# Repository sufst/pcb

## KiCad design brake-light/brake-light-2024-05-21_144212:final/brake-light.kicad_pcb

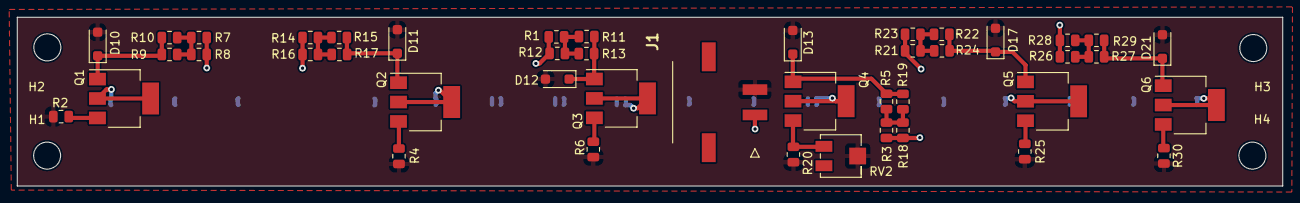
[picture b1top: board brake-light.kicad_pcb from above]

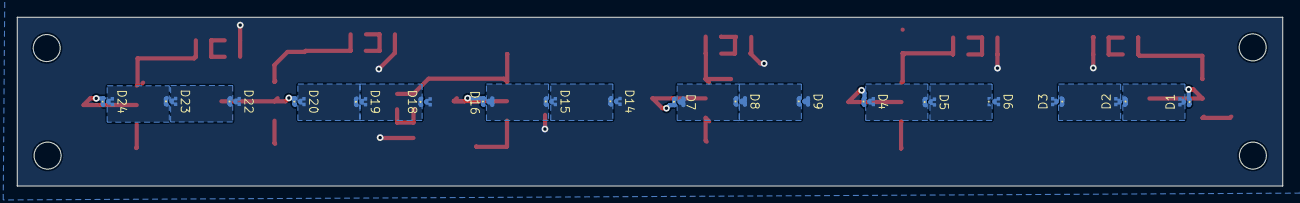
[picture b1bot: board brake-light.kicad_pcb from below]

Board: 2 copper layers, 150.0 x 20.0 mm, 66 parts (18 on the bottom side), 38 nets.

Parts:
D1, D2, D3, D4, D5, D6, D7, D8, D9, D14, D15, D16, D18, D19, D20, D22, D23, D24: KR-SITQA1.23; KR-SITQA1.23_reflow
D10, D11, D12, D13, D17, D21: 1N5333B; D_SOD-123F
H1, H2, H3, H4: MountingHole; MountingHole_3.2mm_M3
J1: LED; Molex_Micro-Fit_3.0_43650-0214_1x02_P3.00mm_Horizontal
Q1, Q2, Q3, Q4, Q5, Q6: BCP56; SOT-223-3_TabPin2
R1, R3, R5, R7, R8, R9, R10, R11, R12, R13, R14, R15, R16, R17, R18, R19, R21, R22, R23, R24, R26, R27, R28, R29: 2.7k; R_0805_2012Metric
R2, R4, R6, R20, R25, R30: 68; R_0805_2012Metric
RV2: R_Potentiometer_Trim; Potentiometer_Bourns_3224J_Horizontal

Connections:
/LED+: D3.2 (A), D6.2 (A), D9.2 (A), D14.2 (A), D18.2 (A), D22.2 (A), J1.1, R1.1, R3.1, R7.1, R8.1, R12.1, R14.1, R16.1, R18.1, R21.1, R23.1, R26.1, R28.1
/LED-: D10.2 (A), D11.2 (A), D12.2 (A), D13.2 (A), D17.2 (A), D21.2 (A), J1.2, R2.2, R4.2, R6.2, R20.2, R25.2, R30.2, RV2.2
unnamed: D1.2 (A), D2.1 (K)
unnamed: D1.1 (K), Q1.2 (C)
unnamed: D2.2 (A), D3.1 (K)
unnamed: D4.2 (A), D5.1 (K)
unnamed: D4.1 (K), Q2.2 (C)
unnamed: D5.2 (A), D6.1 (K)
unnamed: D7.2 (A), D8.1 (K)
unnamed: D7.1 (K), Q3.2 (C)
unnamed: D8.2 (A), D9.1 (K)
unnamed: D10.1 (K), Q1.1 (B), R9.2, R10.2
unnamed: D11.1 (K), Q2.1 (B), R15.2, R17.2
unnamed: D12.1 (K), Q3.1 (B), R11.2, R13.2
unnamed: D13.1 (K), Q4.1 (B), R5.2, R19.2
unnamed: D14.1 (K), D15.2 (A)
unnamed: D15.1 (K), D16.2 (A)
unnamed: D16.1 (K), Q4.2 (C)
unnamed: D17.1 (K), Q5.1 (B), R22.2, R24.2
unnamed: D18.1 (K), D19.2 (A)
unnamed: D19.1 (K), D20.2 (A)
unnamed: D20.1 (K), Q5.2 (C)
unnamed: D21.1 (K), Q6.1 (B), R27.2, R29.2
unnamed: D22.1 (K), D23.2 (A)
unnamed: D23.1 (K), D24.2 (A)
unnamed: D24.1 (K), Q6.2 (C)
unnamed: Q1.3 (E), R2.1
unnamed: Q2.3 (E), R4.1
unnamed: Q3.3 (E), R6.1
unnamed: Q4.3 (E), R20.1, RV2.3
unnamed: Q5.3 (E), R25.1
unnamed: Q6.3 (E), R30.1
unnamed: R1.2, R11.1, R12.2, R13.1
unnamed: R7.2, R8.2, R9.1, R10.1
unnamed: R14.2, R15.1, R16.2, R17.1
unnamed: R3.2, R5.1, R18.2, R19.1
unnamed: R21.2, R22.1, R23.2, R24.1
unnamed: R26.2, R27.1, R28.2, R29.1

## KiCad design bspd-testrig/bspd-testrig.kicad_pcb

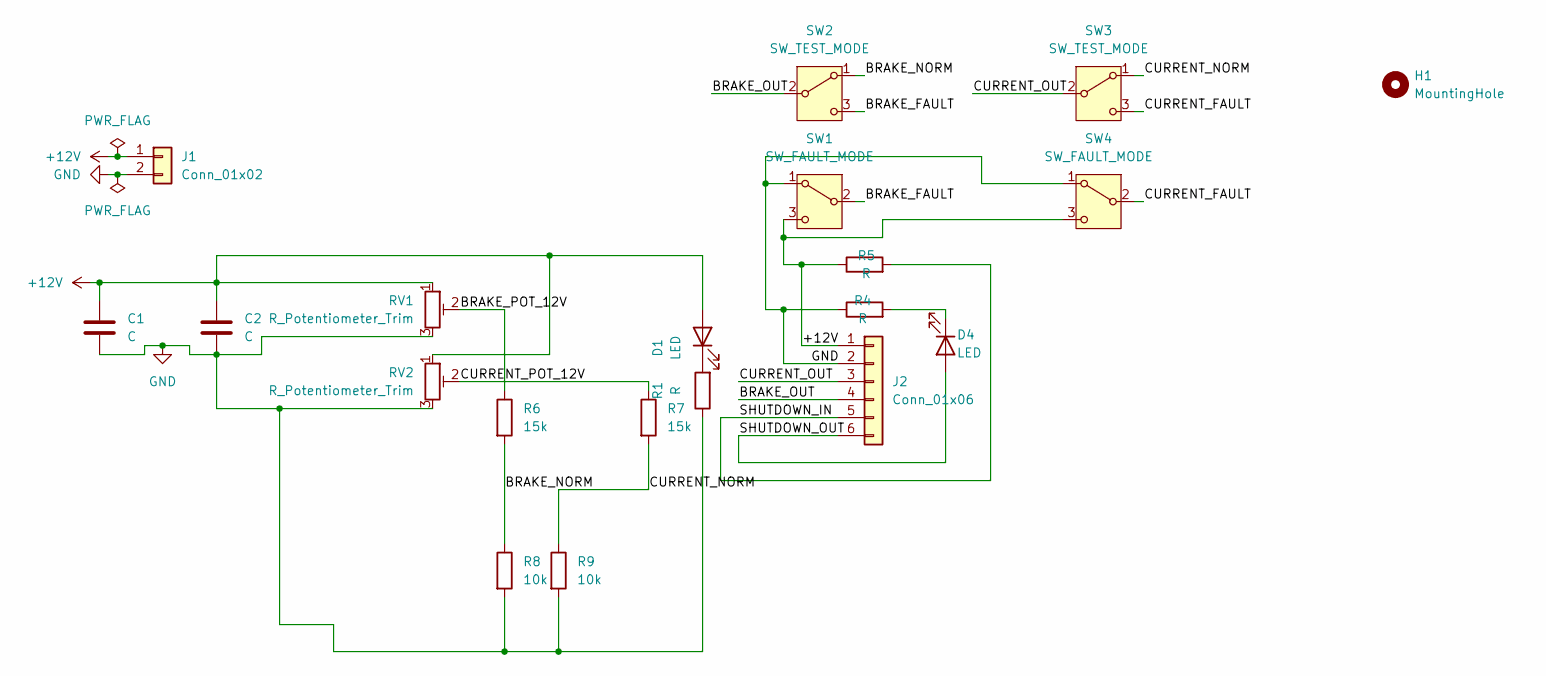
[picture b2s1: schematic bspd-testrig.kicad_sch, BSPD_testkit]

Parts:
C1, C2: C; C_0805_2012Metric_Pad1.18x1.45mm_HandSolder
D1, D4: LED; LED_D3.0mm
H1: MountingHole; MountingHole_3.2mm_M3
J1: Conn_01x02; PinSocket_1x02_P2.54mm_Vertical
J2: Conn_01x06; PinSocket_1x06_P2.54mm_Vertical
R1, R4, R5: R; R_0805_2012Metric_Pad1.20x1.40mm_HandSolder
R6, R7: 15k; R_0805_2012Metric_Pad1.20x1.40mm_HandSolder
R8, R9: 10k; R_0805_2012Metric_Pad1.20x1.40mm_HandSolder
RV1, RV2: R_Potentiometer_Trim; Potentiometer_Alps_RK09K_Single_Vertical
SW1, SW4: SW_FAULT_MODE; SW_Slide_SPDT_Straight_CK_OS102011MS2Q
SW2, SW3: SW_TEST_MODE; SW_Slide_SPDT_Straight_CK_OS102011MS2Q

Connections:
+12V: C1.1, C2.1, D1.2 (A), J1.1, J2.1, R5.1, RV1.1, RV2.1, SW1.3 (C), SW4.3 (C)
/BRAKE_FAULT: SW1.2 (B), SW2.3 (C)
/BRAKE_NORM: R6.2, R8.1, SW2.1 (A)
/BRAKE_OUT: J2.4, SW2.2 (B)
/BRAKE_POT_12V: R6.1, RV1.2
/CURRENT_FAULT: SW3.3 (C), SW4.2 (B)
/CURRENT_NORM: R7.2, R9.1, SW3.1 (A)
/CURRENT_OUT: J2.3, SW3.2 (B)
/CURRENT_POT_12V: R7.1, RV2.2
/SHUTDOWN_IN: J2.5, R5.2
/SHUTDOWN_OUT: D4.2 (A), J2.6
GND: C1.2, C2.2, J1.2, J2.2, R1.1, R4.1, R8.2, R9.2, RV1.3, RV2.3, SW1.1 (A), SW4.1 (A)
unnamed: D1.1 (K), R1.2
unnamed: D4.1 (K), R4.2

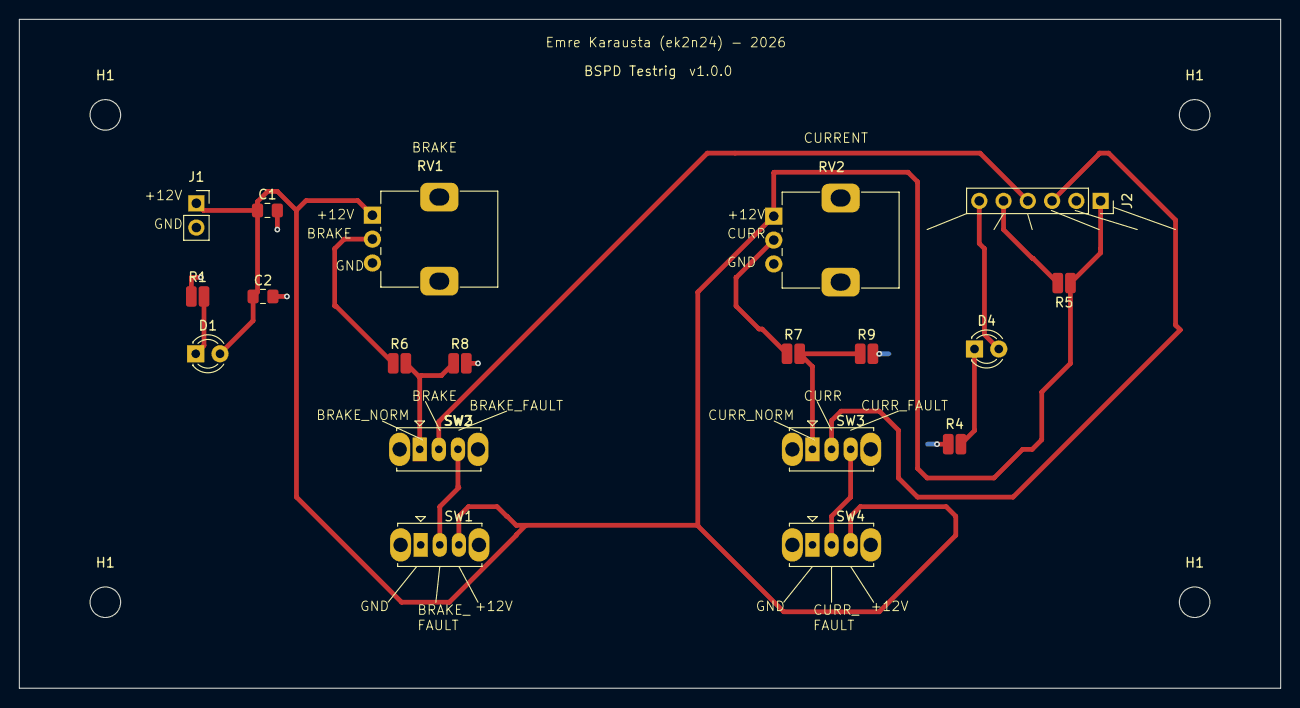
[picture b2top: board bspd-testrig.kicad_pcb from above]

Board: 2 copper layers, 132.0 x 70.0 mm, 23 parts (0 on the bottom side), 14 nets.

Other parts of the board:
H1#2, H1#3, H1#4: MountingHole; MountingHole_3.2mm_M3

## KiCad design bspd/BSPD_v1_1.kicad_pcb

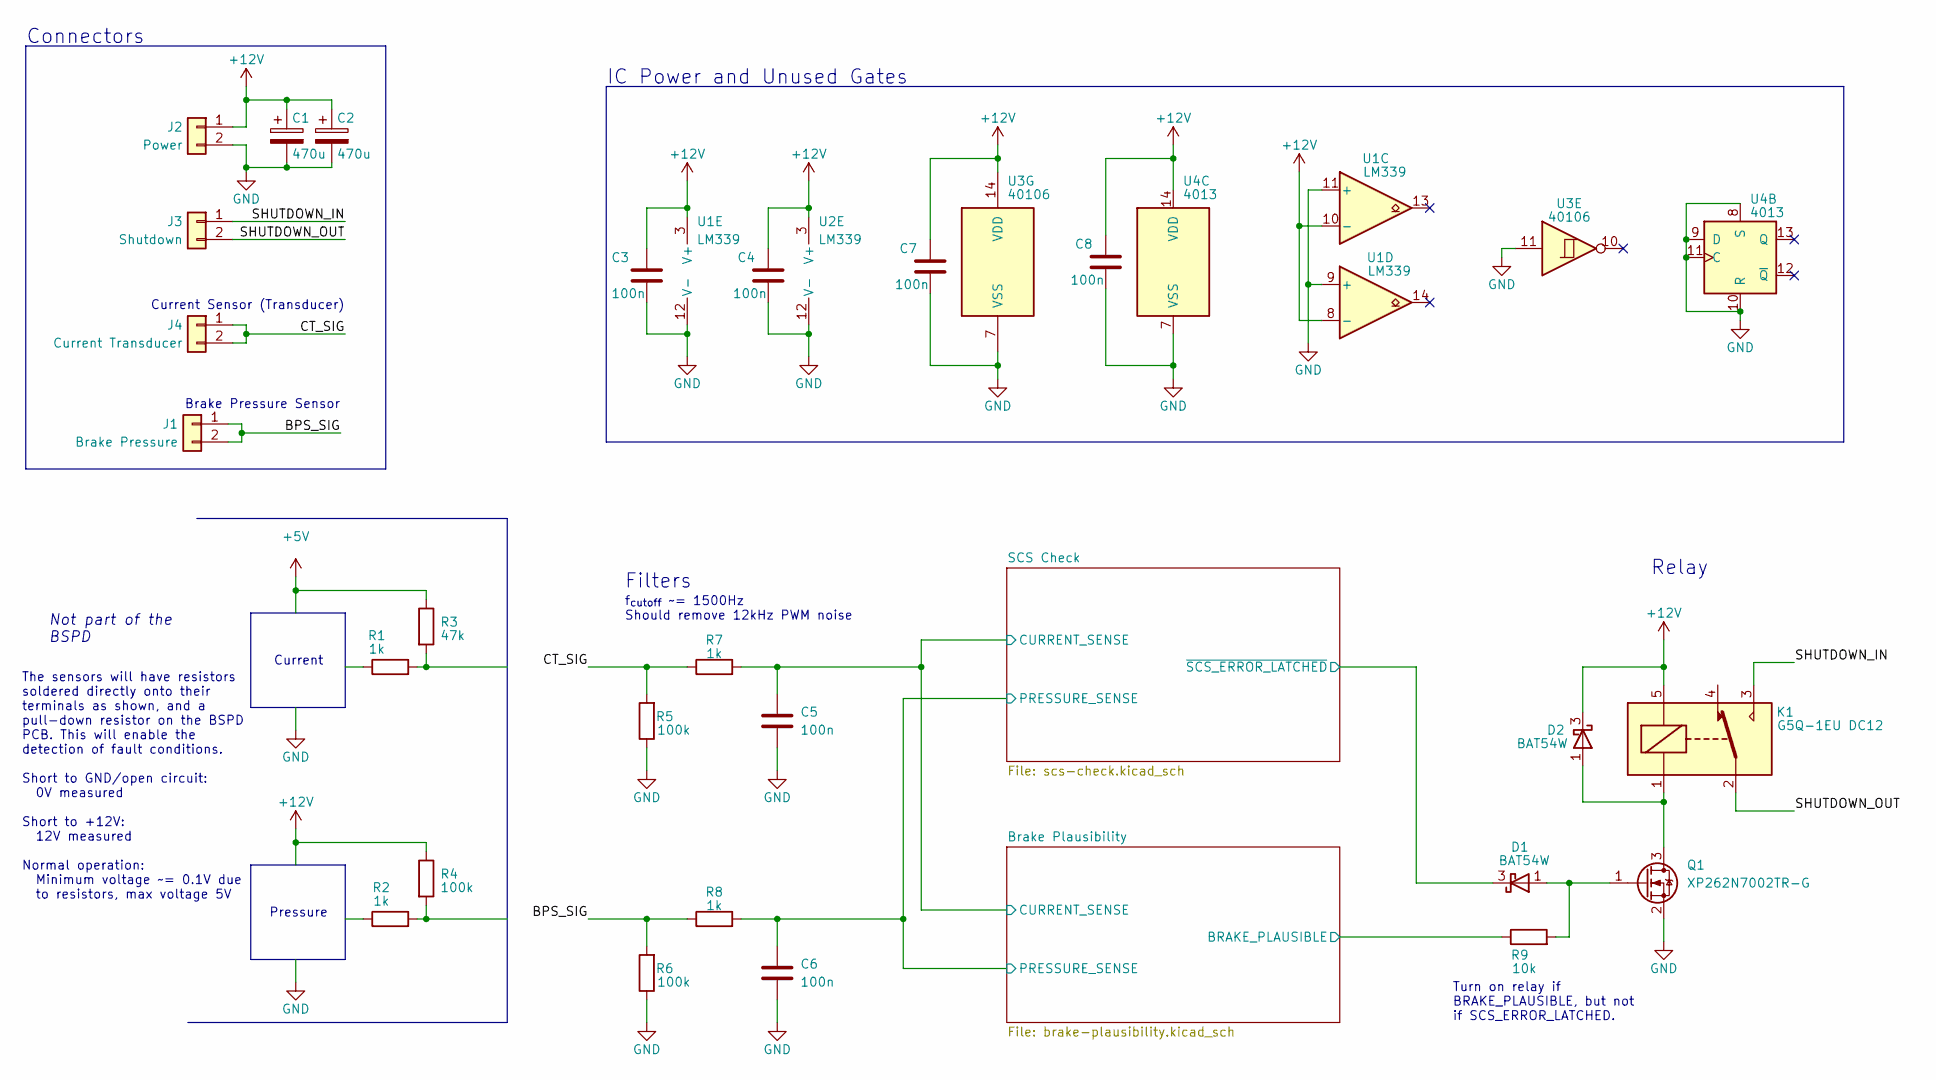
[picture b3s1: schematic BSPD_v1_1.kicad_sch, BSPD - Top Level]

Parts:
C1, C2: 470u
C3, C4, C5, C6, C7, C8: 100n
D1, D2: BAT54W; SOT-323_SC-70
J1: Brake Pressure
J2: Power
J3: Shutdown
J4: Current Transducer
K1: G5Q-1EU DC12; PCH-112L2MH
Q1: XP262N7002TR-G; SOT-23
R1, R2, R7, R8: 1k
R3: 47k
R4, R5, R6: 100k
R9: 10k
U1, U2: LM339
U3: 40106
U4: 4013

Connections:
+12V: C1.1, C2.1, C3.1, C4.1, C7.1, C8.1, D2.3 (K), J2.1, K1.5, R4.1, U1.3 (V+), U1.8 (-), U1.10 (-), U2.3 (V+), U3.14 (VDD), U4.14 (VDD); also elsewhere on the board
/BPS_SIG: J1.1, J1.2, R6.2, R8.1
/Brake Plausibility/BRAKE_PLAUSIBLE: R9.1; also elsewhere on the board
/Brake Plausibility/CURRENT_SENSE: C5.1, R7.2; also elsewhere on the board
/Brake Plausibility/PRESSURE_SENSE: C6.1, R8.2; also elsewhere on the board
/CT_SIG: J4.1, J4.2, R5.2, R7.1
/SCS Check/~SCS_ERROR_LATCHED: D1.3 (K); also elsewhere on the board
/SHUTDOWN_IN: J3.1, K1.3
/SHUTDOWN_OUT: J3.2, K1.2
GND: C1.2, C2.2, C3.2, C4.2, C5.2, C6.2, C7.2, C8.2, J2.2, Q1.2 (S), R5.1, R6.1, U1.9 (+), U1.11 (+), U1.12 (V-), U2.12 (V-), U3.7 (VSS), U3.11, U4.7 (VSS), U4.8 (S), U4.9 (D), U4.10 (R), U4.11 (C); also elsewhere on the board
unnamed: D1.1 (A), Q1.1 (G), R9.2
unnamed: D2.1 (A), K1.1, Q1.3 (D)
unnamed: R1.2, R3.2
unnamed: R2.2, R4.2

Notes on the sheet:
Brake Pressure Sensor
Connectors
f_{cutoff} ~= 1500Hz Should remove 12kHz PWM noise
Current Sensor (Transducer)
Filters
The sensors will have resistors soldered directly onto their terminals as shown, and a pull-down resistor on the BSPD PCB. This will enable the detection of fault conditions. Short to GND/open circuit: 0V measured Short to +12V: 12V measured Normal operation: Minimum voltage ~= 0.1V due to resistor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
Current
IC Power and Unused Gates
Relay
Pressure
Not part of the BSPD
Turn on relay if BRAKE_PLAUSIBLE, but not if SCS_ERROR_LATCHED.

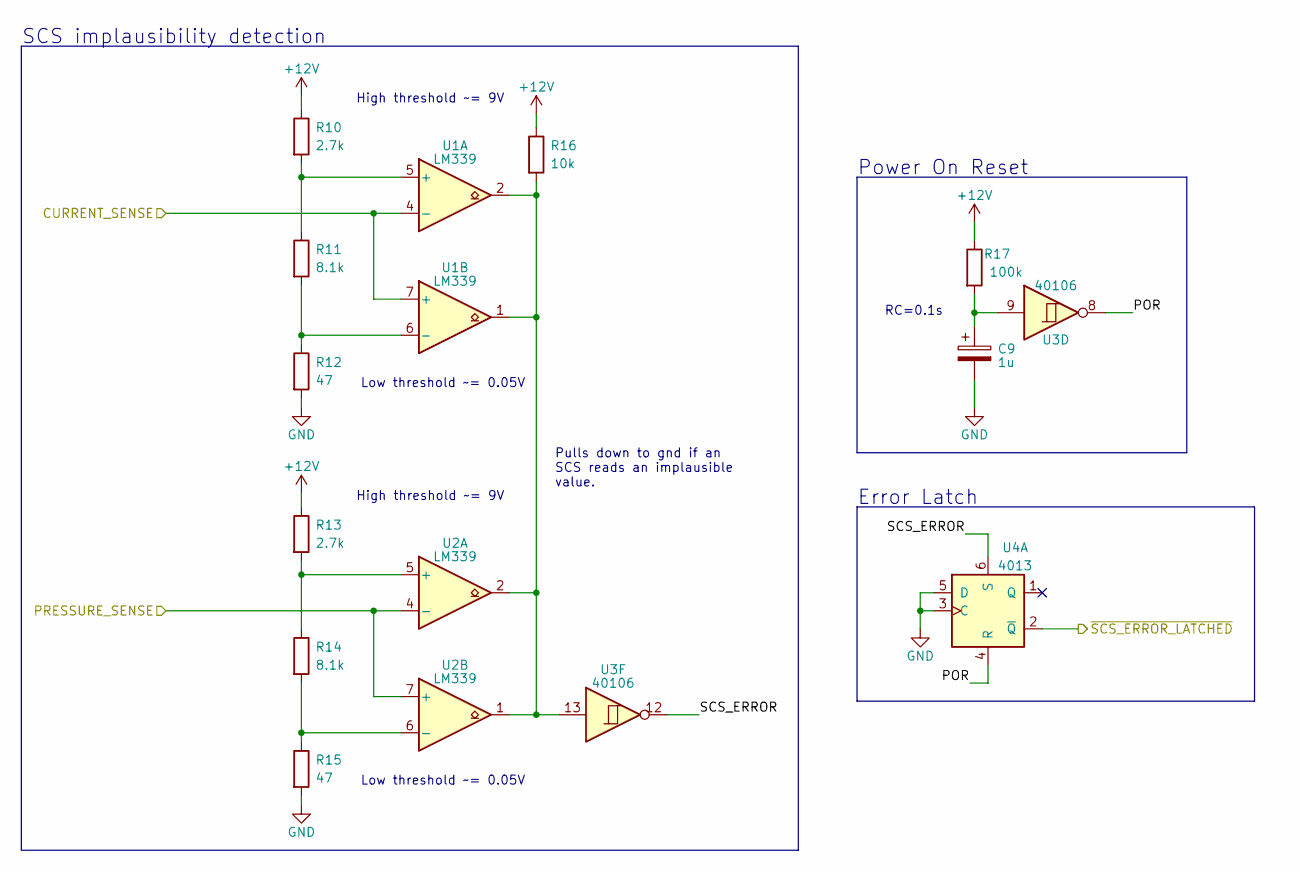
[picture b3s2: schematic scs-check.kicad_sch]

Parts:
C9: 1u; CP_Radial_D5.0mm_P2.00mm
R10, R13: 2.7k
R11, R14: 8.1k
R12, R15: 47
R16: 10k
R17: 100k; R_0603_1608Metric
U1, U2: LM339
U3: 40106
U4: 4013

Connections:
+12V: R10.1, R13.1, R16.1, R17.1; also elsewhere on the board
/Brake Plausibility/CURRENT_SENSE: U1.4 (-), U1.7 (+); also elsewhere on the board
/Brake Plausibility/PRESSURE_SENSE: U2.4 (-), U2.7 (+); also elsewhere on the board
/SCS Check/POR: U3.8, U4.4 (R)
/SCS Check/SCS_ERROR: U3.12, U4.6 (S)
/SCS Check/~SCS_ERROR_LATCHED: U4.2 (~Q); also elsewhere on the board
GND: C9.2, R12.2, R15.2, U4.3 (C), U4.5 (D); also elsewhere on the board
unnamed: C9.1, R17.2, U3.9
unnamed: R10.2, R11.1, U1.5 (+)
unnamed: R11.2, R12.1, U1.6 (-)
unnamed: R13.2, R14.1, U2.5 (+)
unnamed: R14.2, R15.1, U2.6 (-)
unnamed: R16.2, U1.1, U1.2, U2.1, U2.2, U3.13

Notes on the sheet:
RC=0.1s
SCS implausibility detection
High threshold ~= 9V
Low threshold ~= 0.05V
Error Latch
Power On Reset
Pulls down to gnd if an SCS reads an implausible value.

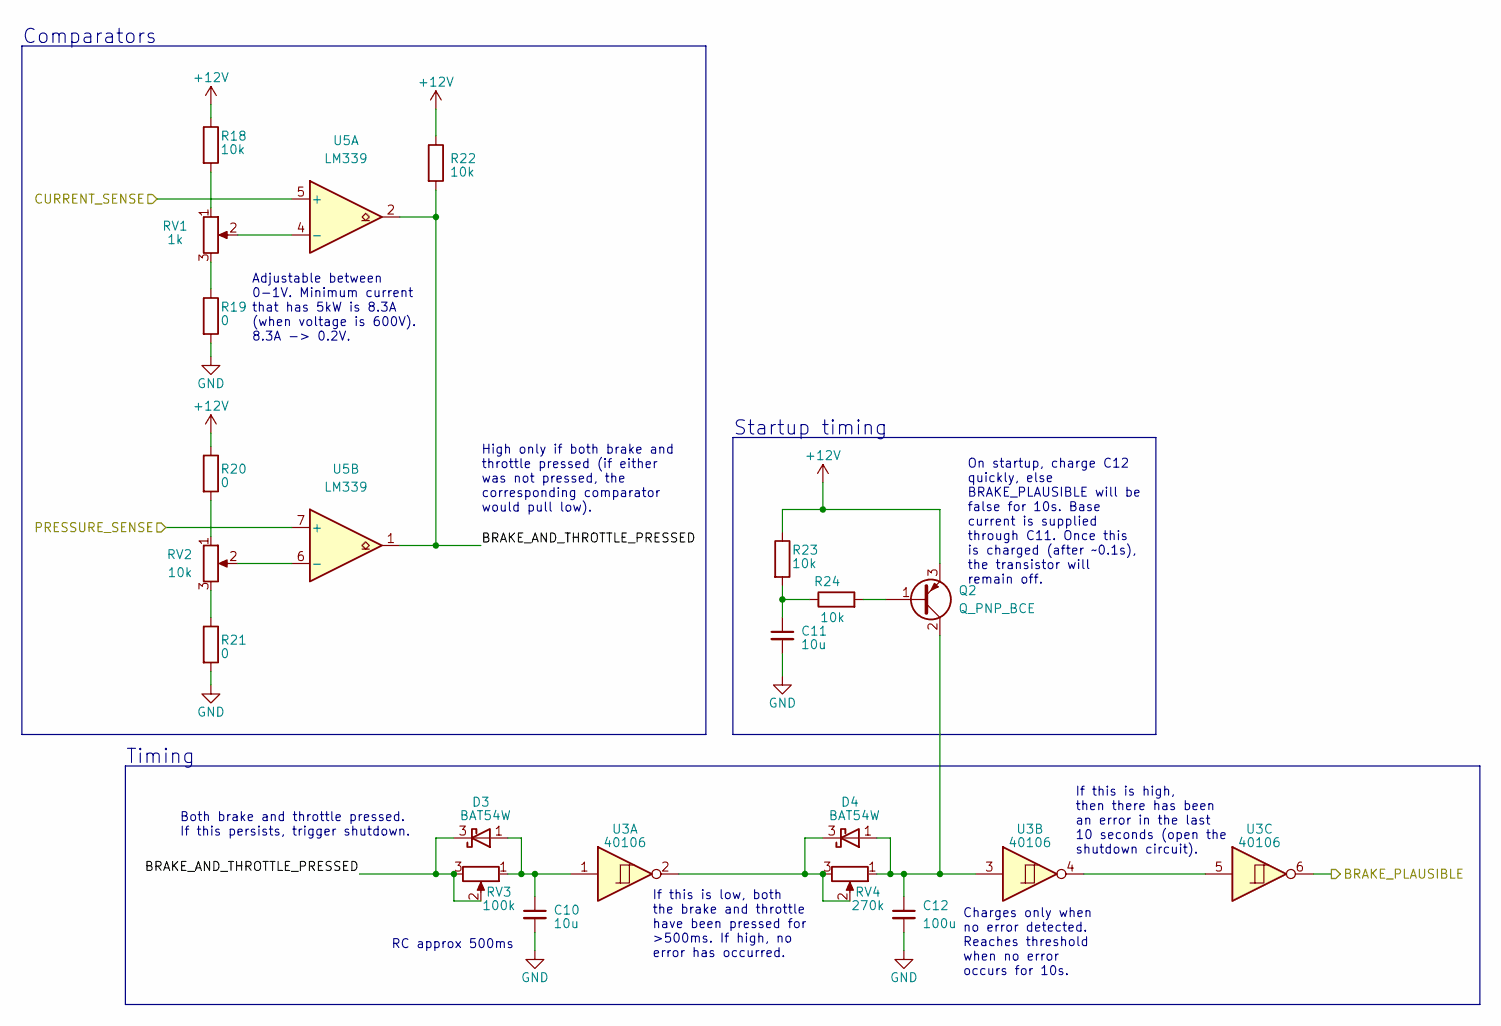
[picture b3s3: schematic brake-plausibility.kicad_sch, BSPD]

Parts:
C10, C11: 10u; CP_Radial_D5.0mm_P2.00mm
C12: 100u; CP_Radial_D10.0mm_P5.00mm
D3, D4: BAT54W; SOT-323_SC-70
Q2: Q_PNP_BCE; TO-92
R18, R22, R23, R24: 10k; R_0603_1608Metric
R19, R20, R21: 0; R_0603_1608Metric
RV1: 1k; Potentiometer_Bourns_3296Y_Vertical
RV2: 10k; Potentiometer_Bourns_3266W_Vertical
RV3: 100k; Potentiometer_Bourns_3299W_Vertical
RV4: 270k; TRIM_3362P-1-304LF
U3: 40106; SOIC-14_3.9x8.7mm_P1.27mm
U5: LM339; SOIC-14_3.9x8.7mm_P1.27mm

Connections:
+12V: Q2.3 (E), R18.1, R20.1, R22.1, R23.1; also elsewhere on the board
/Brake Plausibility/BRAKE_AND_THROTTLE_PRESSED: D3.3 (K), R22.2, RV3.2, RV3.3, U5.1, U5.2
/Brake Plausibility/BRAKE_PLAUSIBLE: U3.6; also elsewhere on the board
/Brake Plausibility/CURRENT_SENSE: U5.5 (+); also elsewhere on the board
/Brake Plausibility/PRESSURE_SENSE: U5.7 (+); also elsewhere on the board
GND: C10.2, C11.2, C12.2, R19.2, R21.2; also elsewhere on the board
unnamed: C10.1, D3.1 (A), RV3.1, U3.1
unnamed: C11.1, R23.2, R24.1
unnamed: C12.1, D4.1 (A), Q2.2 (C), RV4.1, U3.3
unnamed: D4.3 (K), RV4.2, RV4.3, U3.2
unnamed: Q2.1 (B), R24.2
unnamed: R18.2, RV1.1
unnamed: R19.1, RV1.3
unnamed: R20.2, RV2.1
unnamed: R21.1, RV2.3
unnamed: RV1.2, U5.4 (-)
unnamed: RV2.2, U5.6 (-)
unnamed: U3.4, U3.5

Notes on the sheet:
Charges only when no error detected. Reaches threshold when no error occurs for 10s.
RC approx 500ms
Comparators
High only if both brake and throttle pressed (if either was not pressed, the corresponding comparator would pull low).
Both brake and throttle pressed. If this persists, trigger shutdown.
On startup, charge C12 quickly, else BRAKE_PLAUSIBLE will be false for 10s. Base current is supplied through C11. Once this is charged (after ~0.1s), the transistor will remain off.
If this is high, then there has been an error in the last 10 seconds (open the shutdown circuit).
Startup timing
If this is low, both the brake and throttle have been pressed for >500ms. If high, no error has occurred.
Timing
Adjustable between 0-1V. Minimum current that has 5kW is 8.3A (when voltage is 600V). 8.3A -> 0.2V.

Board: 2 copper layers, 56 parts (0 on the bottom side), 33 nets, no tracks yet.

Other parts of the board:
H1, H2, H3, H4: MountingHole; MountingHole_2.1mm

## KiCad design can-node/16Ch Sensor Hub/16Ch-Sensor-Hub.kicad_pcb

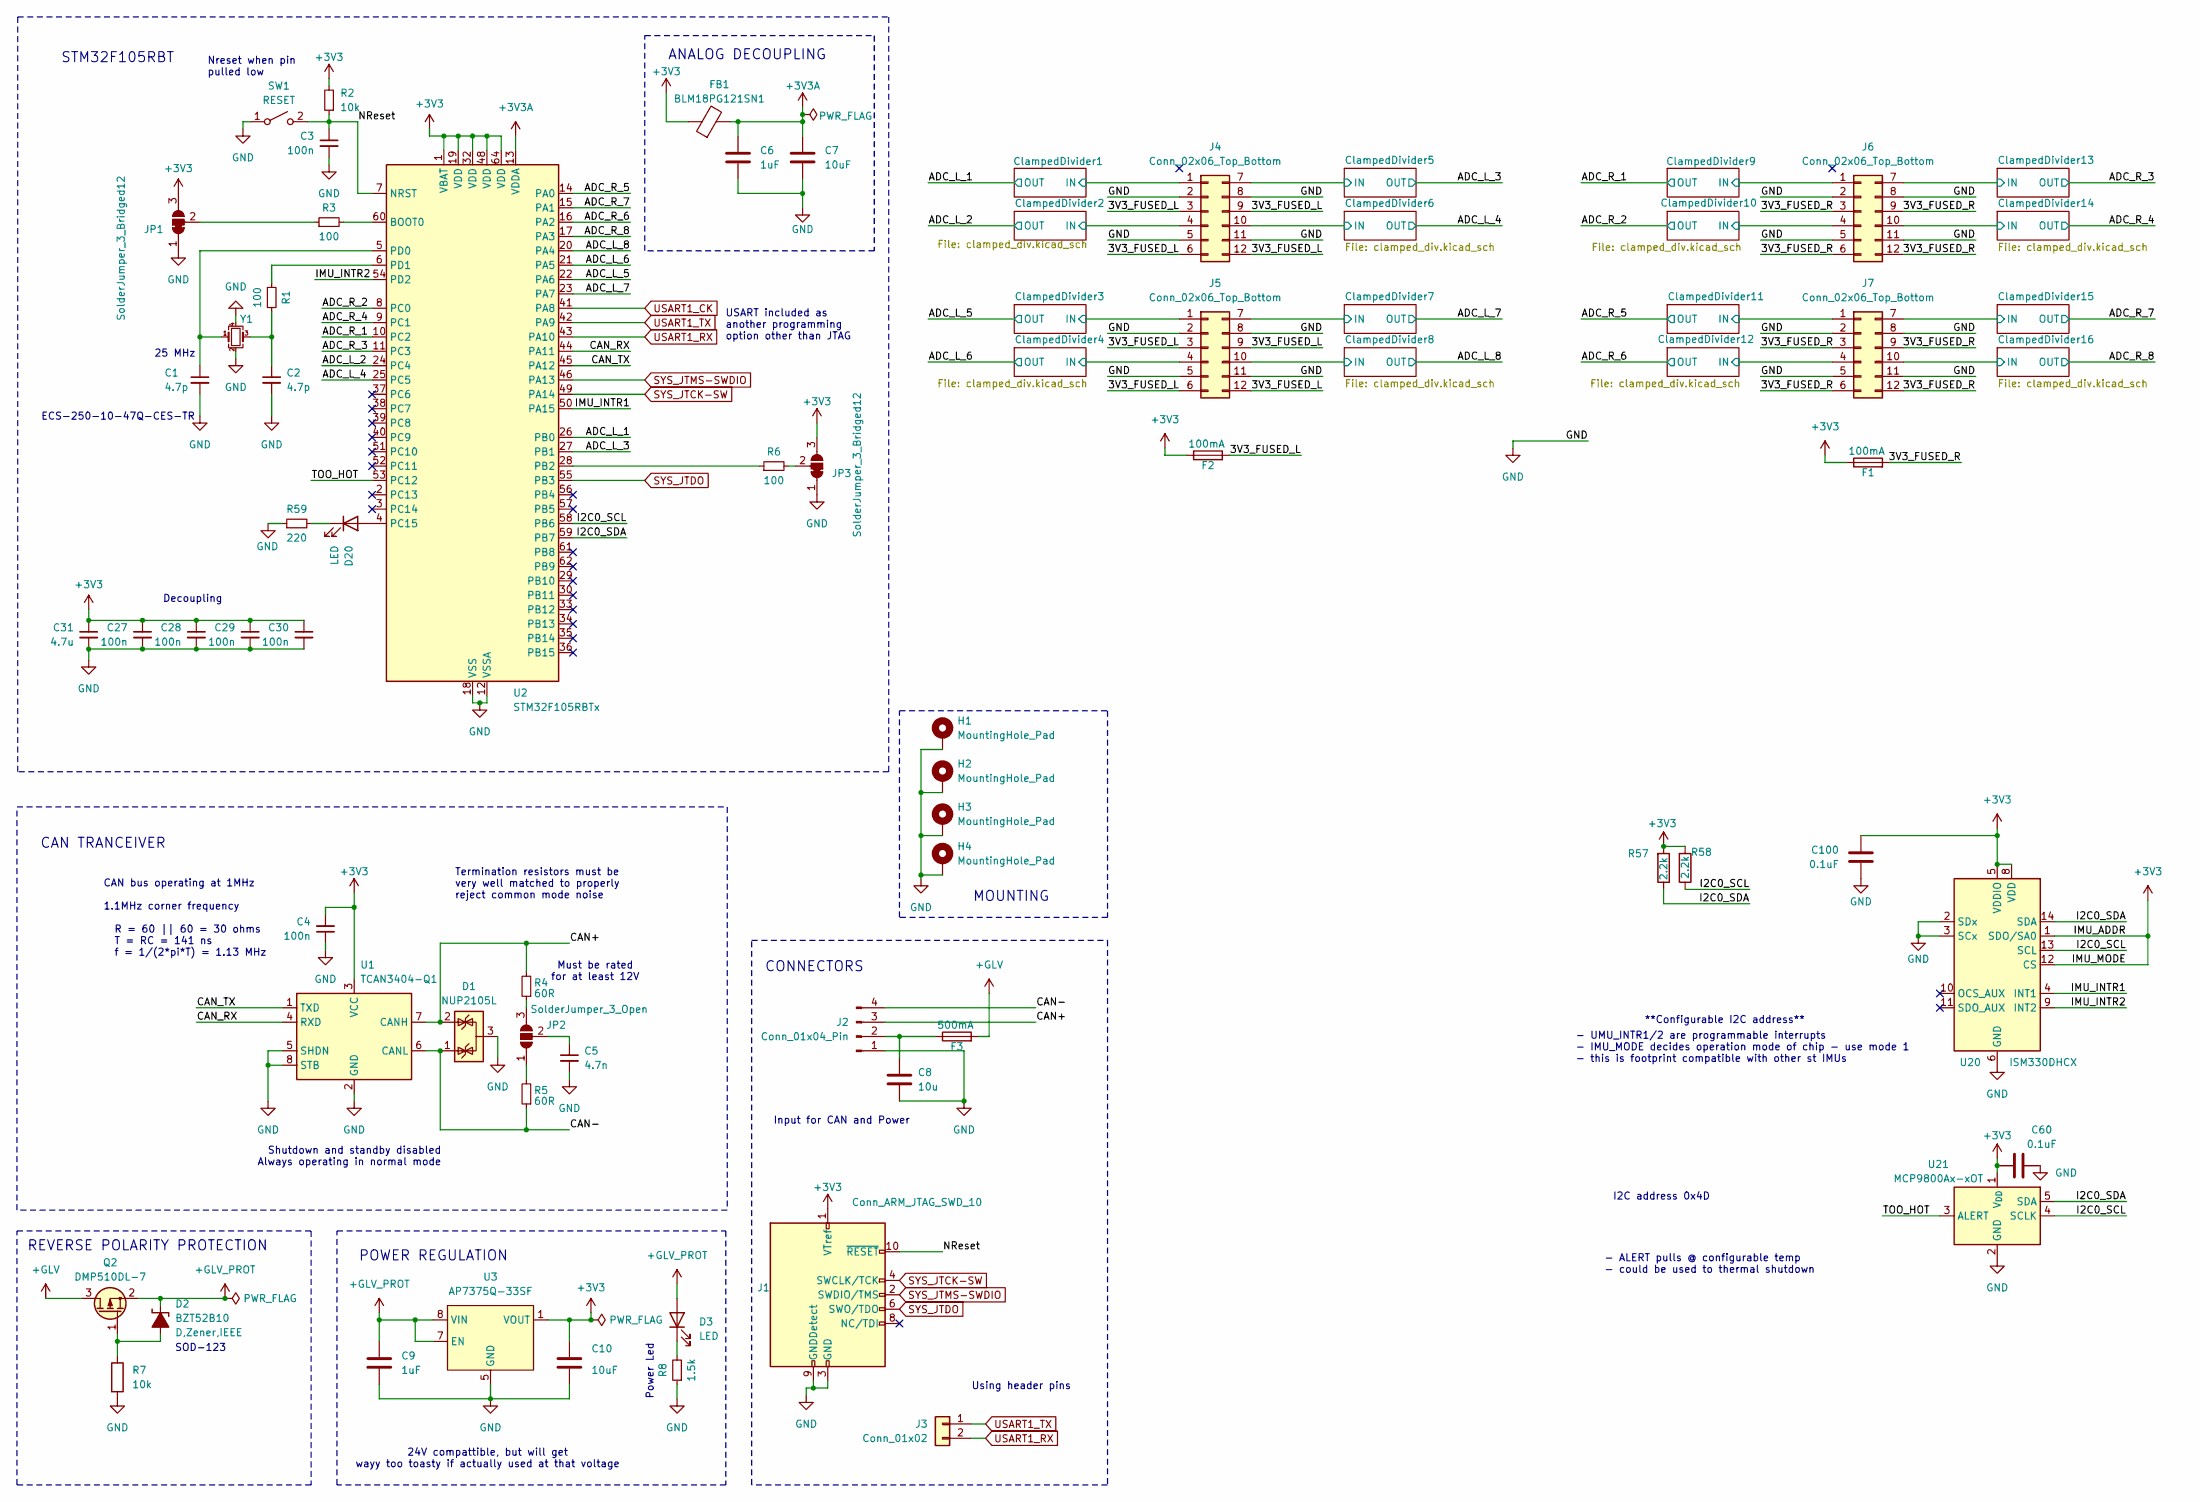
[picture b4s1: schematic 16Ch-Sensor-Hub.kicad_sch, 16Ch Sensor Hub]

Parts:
C1, C2: 4.7p; C_0603_1608Metric_Pad1.08x0.95mm_HandSolder
C3, C4, C27, C28, C29, C30: 100n; C_0603_1608Metric_Pad1.08x0.95mm_HandSolder
C5: 4.7n; C_0603_1608Metric_Pad1.08x0.95mm_HandSolder
C6, C9: 1uF; C_0603_1608Metric_Pad1.08x0.95mm_HandSolder
C7, C10: 10uF; C_0603_1608Metric_Pad1.08x0.95mm_HandSolder
C8: 10u; C_0603_1608Metric_Pad1.08x0.95mm_HandSolder
C31: 4.7u; C_0603_1608Metric_Pad1.08x0.95mm_HandSolder
C60, C100: 0.1uF; C_0603_1608Metric_Pad1.08x0.95mm_HandSolder; Mouser Order Number 81-GRM155R62A104KE4J
D1: NUP2105L; SOT-23; MPN NUP2105L
D2: BZT52B10; D_SOD-123; MPN BZT52B10
D3, D20: LED; LED_0603_1608Metric_Pad1.05x0.95mm_HandSolder
F1, F2: 100mA; Fuse_0603_1608Metric_Pad1.05x0.95mm_HandSolder
F3: 500mA; Fuse_0603_1608Metric_Pad1.05x0.95mm_HandSolder
FB1: BLM18PG121SN1; L_0603_1608Metric_Pad1.05x0.95mm_HandSolder
H1, H2, H3, H4: MountingHole_Pad; MountingHole_3.2mm_M3_Pad_Via
J1: Conn_ARM_JTAG_SWD_10; SHF10501LDSMLC; MPN SHF-105-01-L-D-SM-LC
J2: Conn_01x04_Pin; Molex_Micro-Fit_3.0_43045-0412_2x02_P3.00mm_Vertical
J3: Conn_01x02; PinHeader_1x02_P2.54mm_Vertical
J4, J5, J6, J7: Conn_02x06_Top_Bottom; Molex_Micro-Fit_3.0_43045-1200_2x06_P3.00mm_Horizontal
JP1, JP3: SolderJumper_3_Bridged12; SolderJumper-3_P1.3mm_Bridged12_RoundedPad1.0x1.5mm
JP2: SolderJumper_3_Open; SolderJumper-3_P1.3mm_Open_RoundedPad1.0x1.5mm
Q2: DMP510DL-7; SOT-23
R1, R3, R6: 100; R_0603_1608Metric_Pad0.98x0.95mm_HandSolder
R2, R7: 10k; R_0603_1608Metric_Pad0.98x0.95mm_HandSolder
R4, R5: 60R; R_0603_1608Metric_Pad0.98x0.95mm_HandSolder
R8: 1.5k; R_0603_1608Metric_Pad0.98x0.95mm_HandSolder
R57, R58: 2.2k; R_0603_1608Metric_Pad0.98x0.95mm_HandSolder; Mouser Order Number 603-RC0402FR-072K2L
R59: 220; R_0603_1608Metric_Pad0.98x0.95mm_HandSolder
SW1: RESET; SW_Push_1P1T_NO_CK_KMR2; MPN KMR221NG LFS
U1: TCAN3404-Q1; SOT-23-8_Handsoldering; MPN TCAN3404DDFRQ1
U2: STM32F105RBTx; LQFP-64_10x10mm_P0.5mm
U3: AP7375Q-33SF; Diodes_SO-8EP
U20: ISM330DHCX; LGA-14_3x2.5mm_P0.5mm_LayoutBorder3x4y; Mouser Order Number 511-ISM330DHCXTR
U21: MCP9800Ax-xOT; SOT-23-5; Mouser Order Number 579-MCP9800A5T-M/OT
Y1: ECS-250-10-47Q-CES-TR; Resonator_SMD_ECS_ECX-1247Q_1.6x1.2x0.3mm; MPN ECS-250-10-47Q-CES-TR

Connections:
+3V3: C4.2, C10.1, C27.1, C28.1, C29.1, C30.1, C31.1, C60.1, C100.2, F1.1, F2.1, FB1.1, J1.1 (VTref), JP1.3 (B), JP3.3 (B), R2.2, R57.2, R58.2, U1.3 (VCC), U2.1 (VBAT), U2.19 (VDD), U2.32 (VDD), U2.48 (VDD), U2.64 (VDD), U3.1 (VOUT), U20.1 (SDO/SA0), U20.5 (VDDIO), U20.8 (VDD), U20.12 (CS), U21.1 (V_{DD}); also elsewhere on the board
+3V3A: C6.1, C7.1, FB1.2, U2.13 (VDDA)
+GLV: F3.2, Q2.3 (D)
+GLV_PROT: C9.1, D2.1 (K-), D3.2 (A), Q2.2 (S), U3.7 (EN), U3.8 (VIN)
/3V3_FUSED_L: F2.2, J4.3, J4.6, J4.9, J4.12, J5.3, J5.6, J5.9, J5.12
/3V3_FUSED_R: F1.2, J6.3, J6.6, J6.9, J6.12, J7.3, J7.6, J7.9, J7.12
/ADC_L_1: U2.26 (PB0); also elsewhere on the board
/ADC_L_2: U2.24 (PC4); also elsewhere on the board
/ADC_L_3: U2.27 (PB1); also elsewhere on the board
/ADC_L_4: U2.25 (PC5); also elsewhere on the board
/ADC_L_5: U2.22 (PA6); also elsewhere on the board
/ADC_L_6: U2.21 (PA5); also elsewhere on the board
/ADC_L_7: U2.23 (PA7); also elsewhere on the board
/ADC_L_8: U2.20 (PA4); also elsewhere on the board
/ADC_R_1: U2.10 (PC2); also elsewhere on the board
/ADC_R_2: U2.8 (PC0); also elsewhere on the board
/ADC_R_3: U2.11 (PC3); also elsewhere on the board
/ADC_R_4: U2.9 (PC1); also elsewhere on the board
/ADC_R_5: U2.14 (PA0); also elsewhere on the board
/ADC_R_6: U2.16 (PA2); also elsewhere on the board
/ADC_R_7: U2.15 (PA1); also elsewhere on the board
/ADC_R_8: U2.17 (PA3); also elsewhere on the board
/CAN+: D1.2 (K), J2.3, R4.2, U1.7 (CANH)
/CAN-: D1.1 (K), J2.4, R5.1, U1.6 (CANL)
/CAN_RX: U1.4 (RXD), U2.44 (PA11)
/CAN_TX: U1.1 (TXD), U2.45 (PA12)
/ClampedDivider1/IN: J4.1; also elsewhere on the board
/ClampedDivider2/IN: J4.4; also elsewhere on the board
/ClampedDivider3/IN: J5.1; also elsewhere on the board
/ClampedDivider4/IN: J5.4; also elsewhere on the board
/ClampedDivider5/IN: J4.7; also elsewhere on the board
/ClampedDivider6/IN: J4.10; also elsewhere on the board
/ClampedDivider7/IN: J5.7; also elsewhere on the board
/ClampedDivider8/IN: J5.10; also elsewhere on the board
/ClampedDivider9/IN: J6.1; also elsewhere on the board
/ClampedDivider10/IN: J6.4; also elsewhere on the board
/ClampedDivider11/IN: J7.1; also elsewhere on the board
/ClampedDivider12/IN: J7.4; also elsewhere on the board
/ClampedDivider13/IN: J6.7; also elsewhere on the board
/ClampedDivider14/IN: J6.10; also elsewhere on the board
/ClampedDivider15/IN: J7.7; also elsewhere on the board
/ClampedDivider16/IN: J7.10; also elsewhere on the board
/I2C0_SCL: R58.1, U2.58 (PB6), U20.13 (SCL), U21.4 (SCLK)
/I2C0_SDA: R57.1, U2.59 (PB7), U20.14 (SDA), U21.5 (SDA)
/IMU_INTR1: U2.50 (PA15), U20.4 (INT1)
/IMU_INTR2: U2.54 (PD2), U20.9 (INT2)
/NReset: C3.1, J1.10 (~RESET), R2.1, SW1.2 (B), U2.7 (NRST)
/TOO_HOT: U2.53 (PC12), U21.3 (ALERT)
GND: C1.2, C2.2, C3.2, C4.1, C5.2, C6.2, C7.2, C8.2, C9.2, C10.2, C27.2, C28.2, C29.2, C30.2, C31.2, C60.2, C100.1, D1.3 (A), H1.1, H2.1, H3.1, H4.1, J1.3 (GND), J1.5 (GND), J1.9 (GNDDetect), J2.1, J4.2, J4.5, J4.8, J4.11, J5.2, J5.5, J5.8, J5.11, J6.2, J6.5, J6.8, J6.11, J7.2, J7.5, J7.8, J7.11, JP1.1 (A), JP3.1 (A), R7.2, R8.1, R59.1, SW1.1 (A), U1.2 (GND), U1.5 (SHDN), U1.8 (STB), U2.12 (VSSA), U2.18 (VSS), U2.31 (VSS), U2.47 (VSS), U2.63 (VSS), U3.2, U3.3, U3.4, U3.5 (GND), U3.6, U3.9 (EP), U20.2 (SDx), U20.3 (SCx), U20.6 (GND), U20.7 (GND), U21.2 (GND), Y1.2, Y1.4; also elsewhere on the board
unnamed: C2.1, R1.2, Y1.3
unnamed: D2.2 (A+), Q2.1 (G), R7.1
unnamed: D3.1 (K), R8.2
unnamed: D20.2 (A), U2.4 (PC15)
unnamed: D20.1 (K), R59.2
unnamed: C8.1, F3.1, J2.2
unnamed: JP1.2 (C), R3.1
unnamed: JP2.1 (A), R5.2
unnamed: JP2.3 (B), R4.1
unnamed: C5.1, JP2.2 (C)
unnamed: JP3.2 (C), R6.2
unnamed: R3.2, U2.60 (BOOT0)
unnamed: R6.1, U2.28 (PB2)
unnamed: C1.1, U2.5 (PD0), Y1.1
unnamed: R1.1, U2.6 (PD1)
SYS_JTCK-SW: J1.4 (SWCLK/TCK), U2.49 (PA14)
SYS_JTDO: J1.6 (SWO/TDO), U2.55 (PB3)
SYS_JTMS-SWDIO: J1.2 (SWDIO/TMS), U2.46 (PA13)
USART1_CK: U2.41 (PA8)
USART1_RX: J3.2, U2.43 (PA10)
USART1_TX: J3.1, U2.42 (PA9)

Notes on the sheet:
REVERSE POLARITY PROTECTION
Must be rated for at least 12V
25 MHz
STM32F105RBT
- UMU_INTR1/2 are programmable interrupts - IMU_MODE decides operation mode of chip - use mode 1 - this is footprint compatible with other st IMUs
ANALOG DECOUPLING
Input for CAN and Power
CONNECTORS
I2C address 0x4D
- ALERT pulls @ configurable temp - could be used to thermal shutdown
24V compattible, but will get wayy too toasty if actually used at that voltage
CAN TRANCEIVER
SOD-123
Nreset when pin pulled low
Shutdown and standby disabled Always operating in normal mode
ECS-250-10-47Q-CES-TR
Power Led
**Configurable I2C address**
Decoupling
CAN bus operating at 1MHz 1.1MHz corner frequency R = 60 || 60 = 30 ohms T = RC = 141 ns f = 1/(2*pi*T) = 1.13 MHz
POWER REGULATION
Using header pins
Termination resistors must be very well matched to properly reject common mode noise
USART included as another programming option other than JTAG
MOUNTING

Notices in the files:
parts and their libraries:
License: Apache-2.0
